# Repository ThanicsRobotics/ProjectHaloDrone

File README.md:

# ProjectHalo
This is the official repository of the Thanics Halo open-source project. This is a project powered by the Raspberry Pi Compute Module 3, both the drone and controller use this module, along with several coprocessors. This project is not complete yet and all documaentation has not been uploaded, but feel free to follow along with our progress or use any of our 3D parts or software, as long as you attribute us.
## Background
### The Drone
The Thanics Halo drone utilizes stereo camera vision and ultrasonic sensors to accomplish spherical obstacle avoidance. The Halo drone is built to be versatile with a variety of cameras of different imaging types. The project focuses primarily on 360 (spherical) imaging and spherical video live streaming.

### The Controller
The controller for the Halo drone is equally as innovative as the drone. This is a hybrid controller, able to be used either with two thumbs (traditional), or wrist-mounted for voice or touchscreen control.

## Files
### Software: 
Drone source code is in this repository, the controller code can be found here: https://github.com/ThanicsRobotics/ProjectHaloController
### For ECAD and MCAD Files:
Go to our other repository here: https://github.com/ThanicsRobotics/ProjectHaloCAD

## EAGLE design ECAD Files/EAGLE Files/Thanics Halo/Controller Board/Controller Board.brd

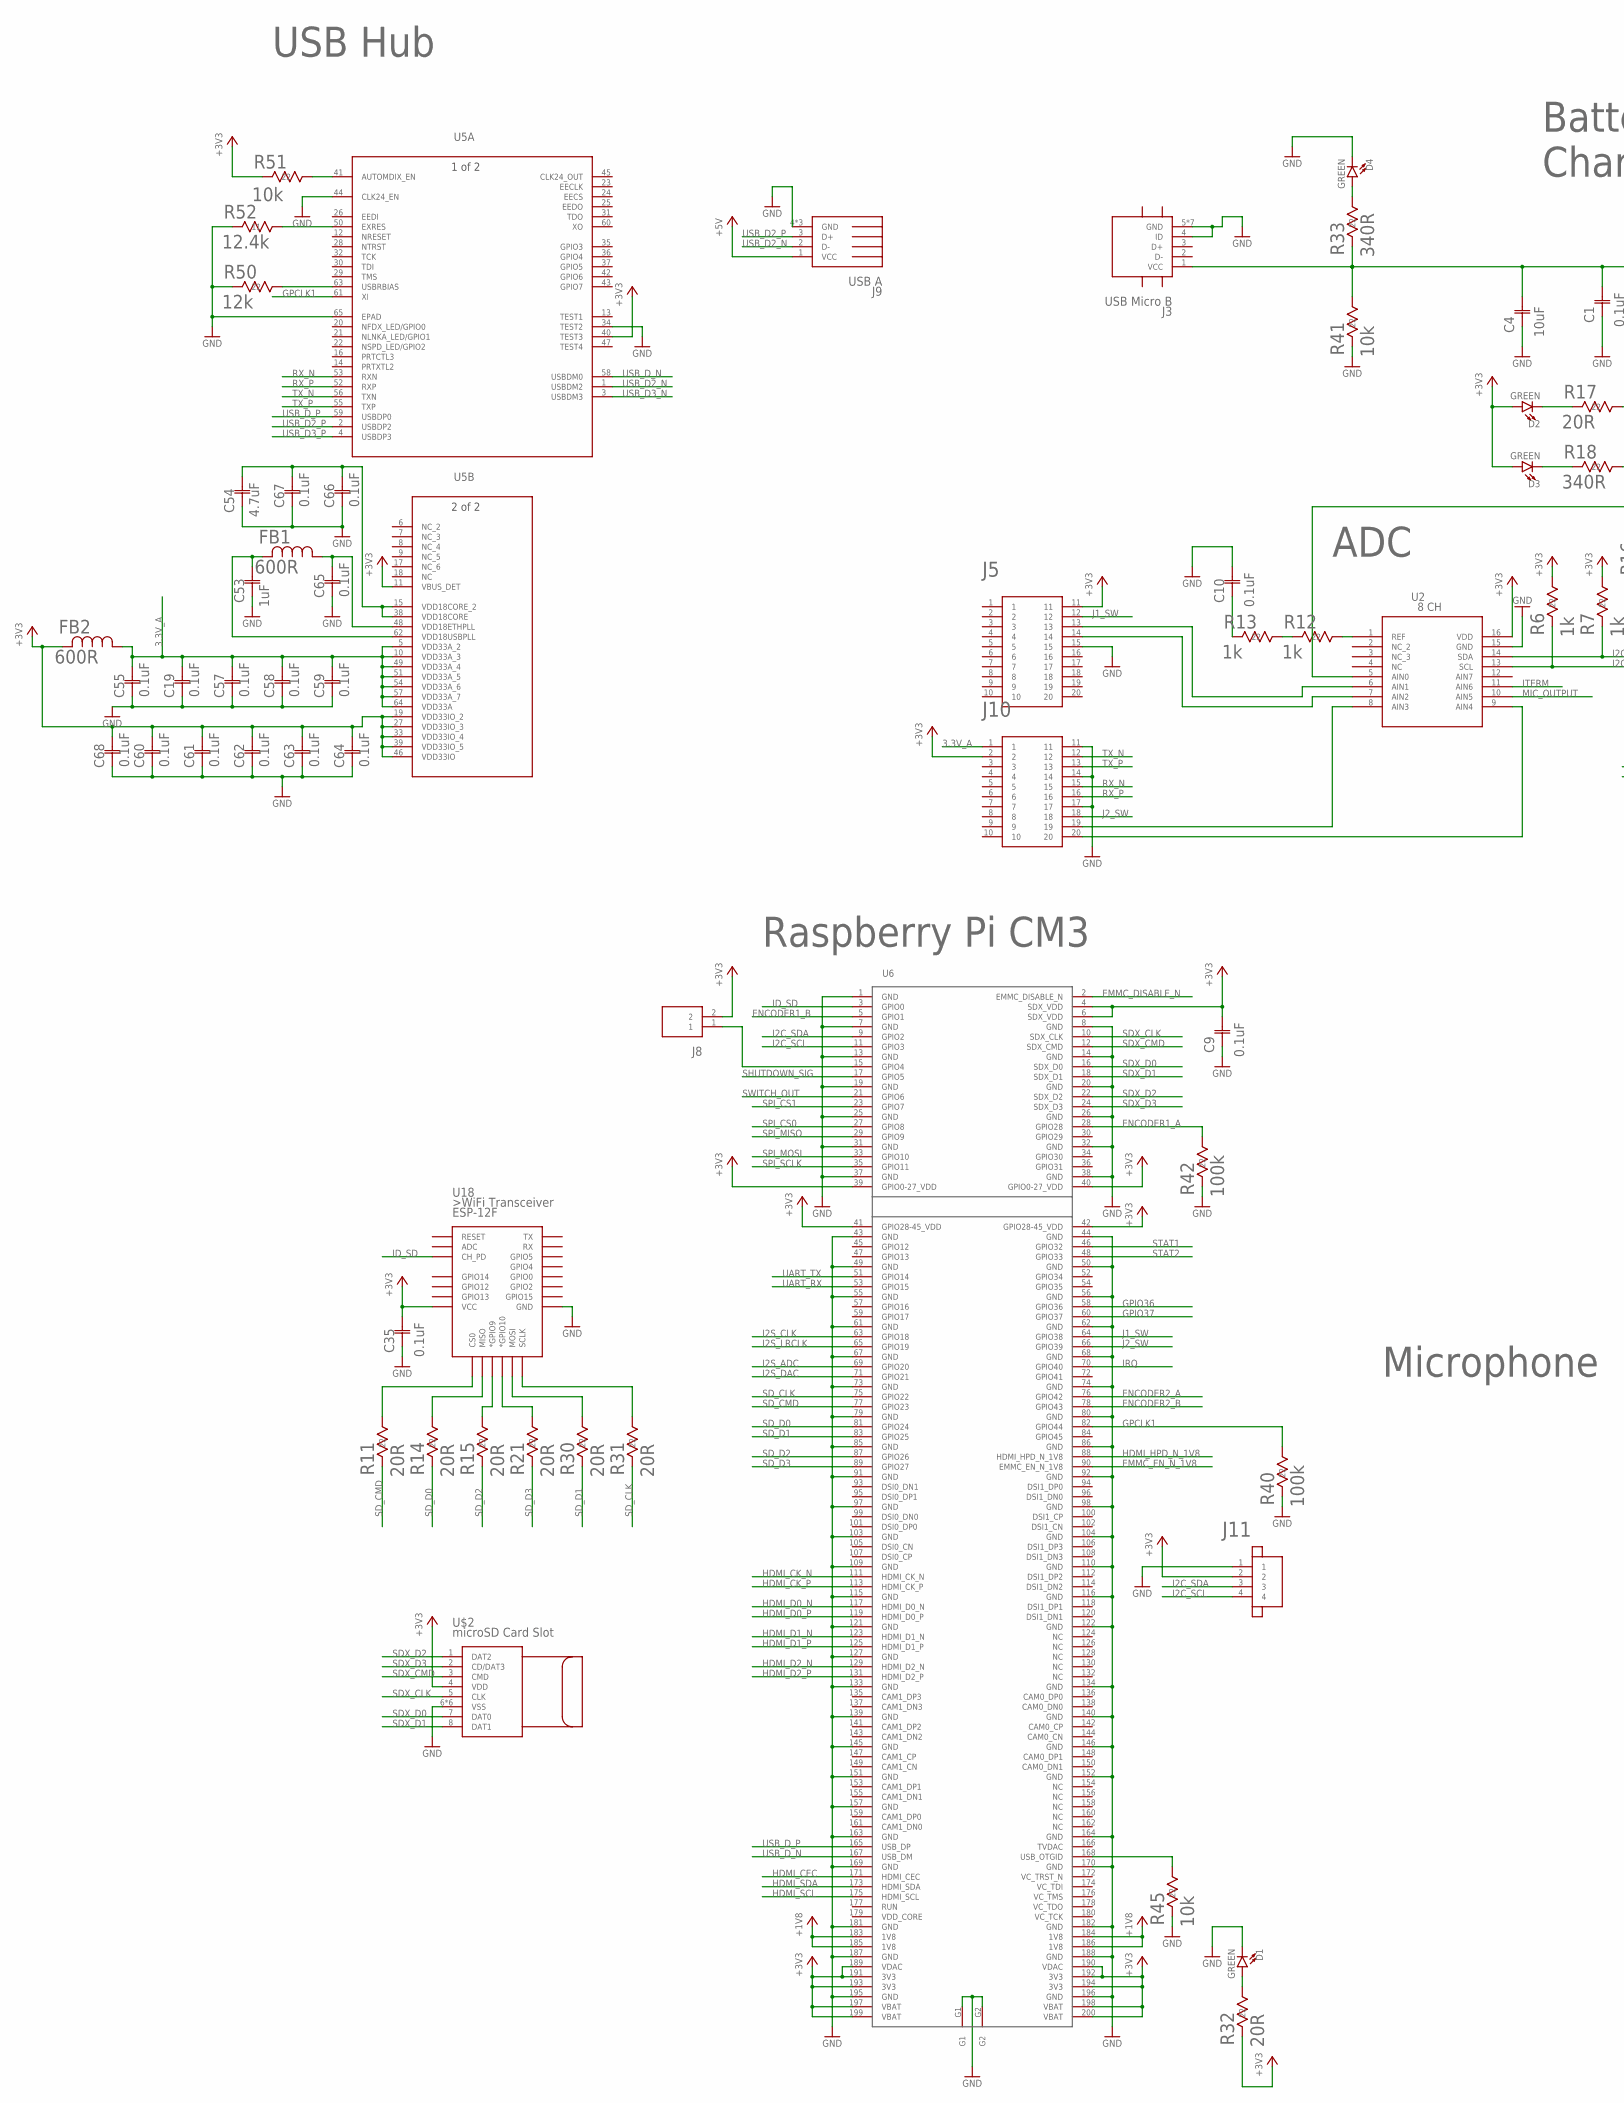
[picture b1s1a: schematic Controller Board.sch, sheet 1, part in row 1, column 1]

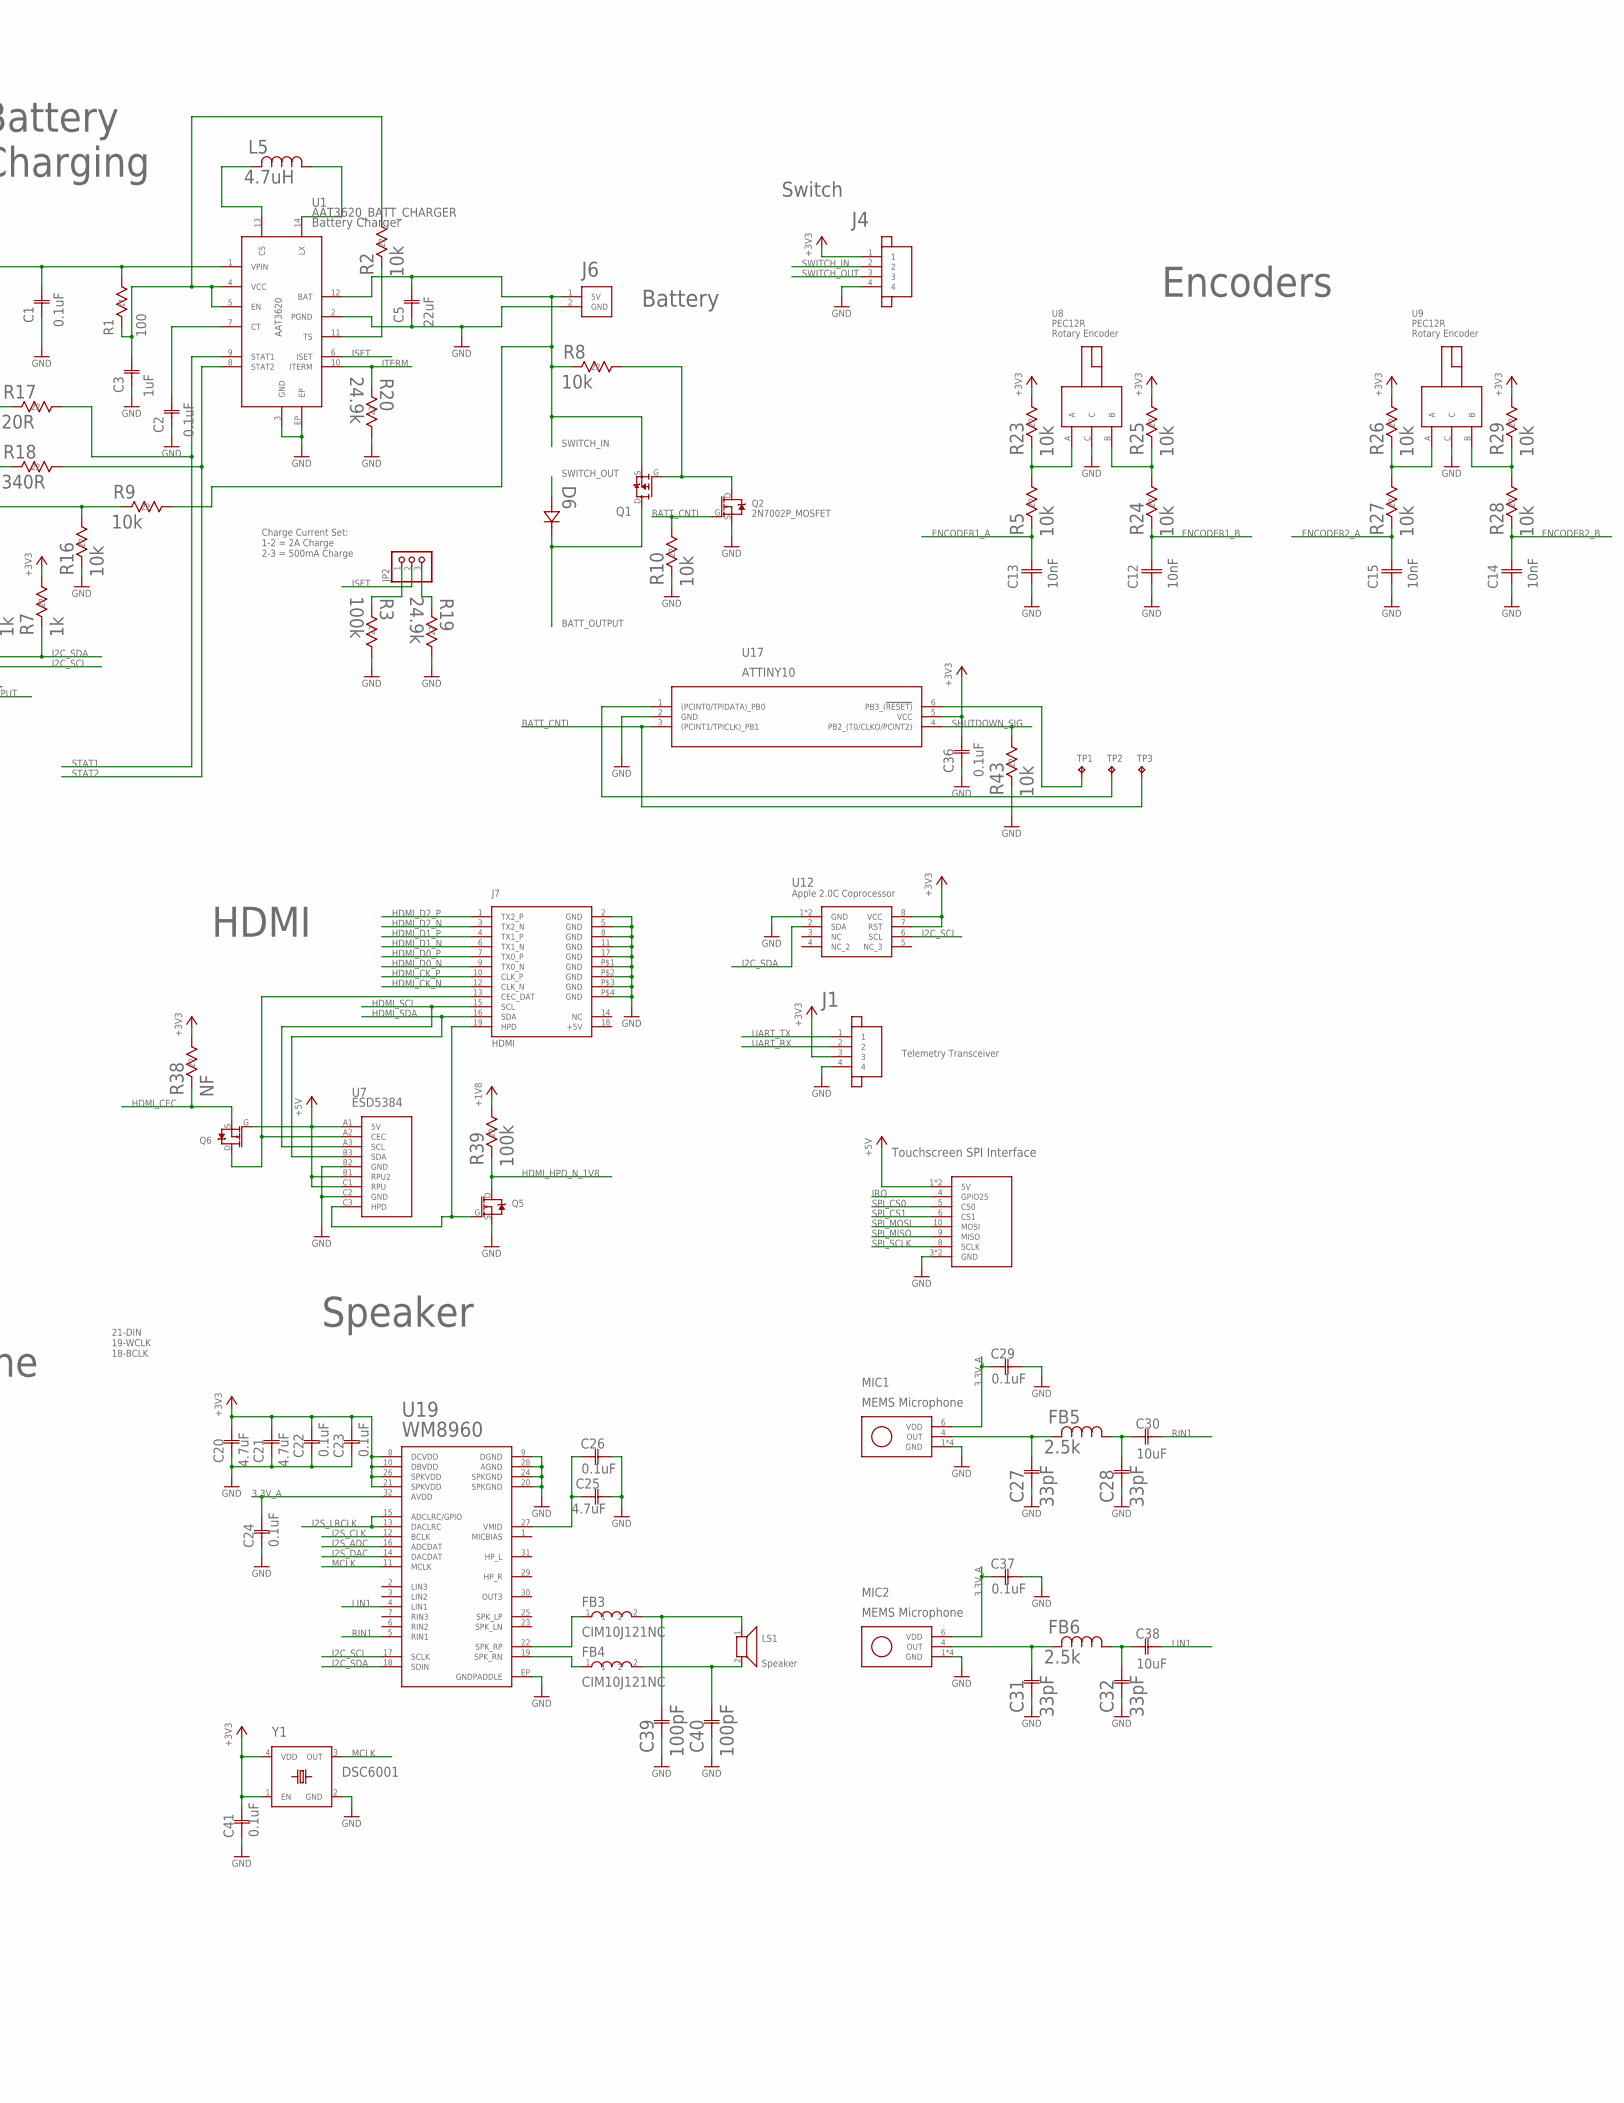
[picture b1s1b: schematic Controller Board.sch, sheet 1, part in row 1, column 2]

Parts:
C1, C2, C9, C10, C35, C36: 0.1uF; 0805
C3, C53: 1uF; YAG_CC0805
C4, C30, C38: 10uF; G-21
C5: 22uF; G-21
C12, C13, C14, C15: 10nF; 0603_CAPACITOR
C19, C22, C23, C24, C26, C29, C37, C41, C55, C57, C58, C59, C60, C61, C62, C63, C64, C65, C66, C67, C68: 0.1uF; 0402-M
C20, C21, C25, C54: 4.7uF; 0603-M
C27, C28, C31, C32: 33pF; G-155-M
C39, C40: 100pF; YAG_CC0402-M
D1, D2, D3, D4: GREEN; LED-0603
D6: 1N4148W-7-FSOD123-M; SOD123-M
FB1, FB2: 600R; IND_BLM18_0603-M
FB3, FB4: CIM10J121NC; 0603_CAPACITOR
FB5, FB6: 2.5k; IND_BLM18_0603-M
J1, J4, J11: JST_SH_4POS
J2: 3.5_TOUCHSCREEN
J3: USB_MICRO_B_SMT
J5, J10: EDGE_CONNECTOR_20POS
J6: POWER_CONNECTOR; XH_CONNECTOR
J7: HDMI
J8: 2_PIN_CONNECTOR; XH_CONNECTOR
J9: USB_A_RECEPT
JP2: PINHD-1X3; 1X03
L5: 4.7uH; 1008
LS1: SP-1510; SPEAKER
MIC1, MIC2: SPH1642HT5H-1; SISONIC_MICROPHONE
Q1: DMP3099L; SOT-23_(TO-236AB)
Q2: 2N7002P_MOSFET; SOT-23_(TO-236AB)
Q5, Q6: DMG1012T; SOT-523
R1: 100; 1206
R2, R5, R8, R9, R10, R16, R23, R24, R25, R26, R27, R28, R29, R41, R43, R45, R51: 10k; RC0805N
R3, R39, R40, R42: 100k; RC0603N-M
R6, R7, R12, R13: 1k; RC0603N-M
R11, R14, R15, R17, R21, R30, R31, R32: 20R; RC0603N-M
R18, R33: 340R; RC0603N
R19, R20: 24.9k; RC0402N-M
R38: NF; RC0805N
R50: 12k; RC0402N-M
R52: 12.4k; YAG_R0402-M
TP1, TP2, TP3: TPB2,54; B2,54
U1: AAT3620_BATT_CHARGER; AAT3620_TDFN
U2: 8 CH; 21-0055H_16-M
U5: LAN9512-JZXQFN64_9X9MC-M; QFN64_9X9MC-M
U6: COMPUTE_MODULE; SO-DIMM
U7: ESD5384; WLCSP9
U8, U9: PEC12R
U12: APPLE_2.0C_COPROCESSOR; PG-USON-8-1
U17: ATTINY10-TSHR6ST1-M; 6ST1-M
U18: ESP12ESMD; ESP12E-SMD
U19: WM8960; 32QFN
U$2: MICROSD
Y1: DSC6001; 4-VFLGA

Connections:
3.3V_A: C19.2, C24.2, C29.1, C37.1, C55.2, C57.2, C58.2, C59.2, FB2.1, J10.1, MIC1.6 (VDD), MIC2.6 (VDD), U5.5 (VDD33A_2), U5.10 (VDD33A_3), U5.49 (VDD33A_4), U5.51 (VDD33A_5), U5.54 (VDD33A_6), U5.57 (VDD33A_7), U5.64 (VDD33A), U19.32 (AVDD)
+1V8: R39.1 (11), U6.183 (1V8), U6.184 (1V8), U6.185 (1V8), U6.186 (1V8); also elsewhere on the board
+3V3: C9.2, C20.2, C21.2, C22.2, C23.2, C35.2, C36.2, C41.2, C60.2, C61.2, C62.2, C63.2, C64.2, C68.2, D2.A, D3.A, FB2.2, J1.3, J4.1, J5.11, J8.2, J10.2, J11.2, R6.1 (11), R7.1 (11), R23.1 (11), R25.1 (11), R26.1 (11), R29.1 (11), R32.2 (22), R38.1 (11), R51.2 (22), U2.16 (VDD), U5.11 (VBUS_DET), U5.19 (VDD33IO_2), U5.27 (VDD33IO_3), U5.33 (VDD33IO_4), U5.39 (VDD33IO_5), U5.40 (TEST3), U5.46 (VDD33IO), U6.4 (SDX_VDD), U6.6 (SDX_VDD), U6.39 (GPIO0-27_VDD), U6.40 (GPIO0-27_VDD), U6.41 (GPIO28-45_VDD), U6.42 (GPIO28-45_VDD), U6.189 (VDAC), U6.190 (VDAC), U6.191 (3V3), U6.192 (3V3), U6.193 (3V3), U6.194 (3V3), U6.197 (VBAT), U6.198 (VBAT), U6.199 (VBAT), U6.200 (VBAT), U12.7 (RST), U12.8 (VCC), U17.5 (VCC), U18.VCC, U19.8 (DCVDD), U19.10 (DBVDD), U19.21 (SPKVDD), U19.26 (SPKVDD), U$2.4 (VDD), Y1.1 (EN), Y1.4 (VDD); also elsewhere on the board
+5V: J2.1 (5V), J2.2 (5V), J9.1 (VCC), Q6.G, U7.A1 (5V), U7.B1 (RPU2), U7.C1 (RPU); also elsewhere on the board
BATT_CNTL: Q2.G, R10.1 (11), TP3.TP, U17.3 ((PCINT1/TPICLK)_PB1)
BATT_OUTPUT: D6.C (12), Q1.D; also elsewhere on the board
EMMC_DISABLE_N: U6.2 (EMMC_DISABLE_N)
EMMC_EN_N_1V8: U6.90 (EMMC_EN_N_1V8)
ENCODER1_A: C13.2, R5.2 (22), R42.1 (11), U6.28 (GPIO28)
ENCODER1_B: C12.2, R24.2 (22), U6.5 (GPIO1)
ENCODER2_A: C15.2, R27.2 (22), U6.76 (GPIO42)
ENCODER2_B: C14.2, R28.2 (22), U6.78 (GPIO43)
GND: C1.1, C2.1, C3.1, C4.1, C5.1, C9.1, C10.2, C12.1, C13.1, C14.1, C15.1, C19.1, C20.1, C21.1, C22.1, C23.1, C24.1, C25.2, C26.2, C27.1 (11), C28.1 (11), C29.2, C31.1 (11), C32.1 (11), C35.1, C36.1, C37.2, C39.1 (11), C40.1 (11), C41.1, C53.1 (11), C54.1, C55.1, C57.1, C58.1, C59.1, C60.1, C61.1, C62.1, C63.1, C64.1, C65.1, C66.1, C67.1, C68.1, D1.C, D4.C, J1.4, J2.3 (GND), J2.7 (GND), J3.4 (ID), J3.5 (GND), J3.6 (GND), J3.7 (GND), J3.P$1 (GND), J3.P$2 (GND), J3.P$3 (GND), J3.P$4 (GND), J4.4, J5.15, J6.2 (GND), J7.2 (GND), J7.5 (GND), J7.8 (GND), J7.11 (GND), J7.17 (GND), J7.P$1 (GND), J7.P$2 (GND), J7.P$3 (GND), J7.P$4 (GND), J9.4 (GND), J9.5 (GND), J9.6 (GND), J10.11, J10.14, J10.17, J11.1, MIC1.1 (GND), MIC1.2 (GND), MIC1.3 (GND), MIC1.5 (GND), MIC2.1 (GND), MIC2.2 (GND), MIC2.3 (GND), MIC2.5 (GND), Q2.S, Q5.S, R3.1 (11), R10.2 (22), R16.2 (22), R19.1 (11), R20.1 (11), R40.2 (22), R41.2 (22), R42.2 (22), R43.2 (22), R45.2 (22), R50.2 (22), R52.1 (11), U1.2 (PGND), U1.3 (GND), U1.EP, U2.15 (GND), U5.34 (TEST2), U5.44 (CLK24_EN), U5.65 (EPAD), U6.1 (GND), U6.7 (GND), U6.8 (GND), U6.13 (GND), U6.14 (GND), U6.19 (GND), U6.20 (GND), U6.25 (GND), U6.26 (GND), U6.31 (GND), U6.32 (GND), U6.37 (GND), U6.38 (GND), U6.43 (GND), U6.44 (GND), U6.49 (GND), U6.50 (GND), U6.55 (GND), U6.56 (GND), U6.61 (GND), U6.62 (GND), U6.67 (GND), U6.68 (GND), U6.73 (GND), U6.74 (GND), U6.79 (GND), U6.80 (GND), U6.85 (GND), U6.86 (GND), U6.91 (GND), U6.92 (GND), U6.97 (GND), U6.98 (GND), U6.103 (GND), U6.104 (GND), U6.109 (GND), U6.110 (GND), U6.115 (GND), U6.116 (GND), U6.121 (GND), U6.122 (GND), U6.127 (GND), U6.133 (GND), U6.134 (GND), U6.139 (GND), U6.140 (GND), U6.145 (GND), U6.146 (GND), U6.151 (GND), U6.152 (GND), U6.157 (GND), U6.163 (GND), U6.164 (GND), U6.169 (GND), U6.170 (GND), U6.181 (GND), U6.182 (GND), U6.187 (GND), U6.188 (GND), U6.195 (GND), U6.196 (GND), U6.G1, U6.G2, U7.B2 (GND), U7.C2 (GND), U8.C, U9.C, U12.1 (GND), U12.9 (GND), U17.2 (GND), U18.GND, U19.9 (DGND), U19.20 (SPKGND), U19.24 (SPKGND), U19.28 (AGND), U19.EP (GNDPADDLE), U$2.6 (VSS), U$2.9 (VSS), U$2.10 (VSS), U$2.11 (VSS), U$2.12 (VSS), U$2.13 (VSS), Y1.2 (GND); also elsewhere on the board
GPCLK1: R40.1 (11), U5.61 (XI), U6.82 (GPIO44)
GPIO36: U6.58 (GPIO36)
GPIO37: U6.60 (GPIO37)
HDMI_CEC: Q6.S, R38.2 (22), U6.171 (HDMI_CEC)
HDMI_CK_N: J7.12 (CLK_N), U6.111 (HDMI_CK_N)
HDMI_CK_P: J7.10 (CLK_P), U6.113 (HDMI_CK_P)
HDMI_D0_N: J7.9 (TX0_N), U6.117 (HDMI_D0_N)
HDMI_D0_P: J7.7 (TX0_P), U6.119 (HDMI_D0_P)
HDMI_D1_N: J7.6 (TX1_N), U6.123 (HDMI_D1_N)
HDMI_D1_P: J7.4 (TX1_P), U6.125 (HDMI_D1_P)
HDMI_D2_N: J7.3 (TX2_N), U6.129 (HDMI_D2_N)
HDMI_D2_P: J7.1 (TX2_P), U6.131 (HDMI_D2_P)
HDMI_HPD_N_1V8: Q5.D, R39.2 (22), U6.88 (HDMI_HPD_N_1V8)
HDMI_SCL: J7.15 (SCL), U6.175 (HDMI_SCL), U7.A3 (SCL)
HDMI_SDA: J7.16 (SDA), U6.173 (HDMI_SDA), U7.B3 (SDA)
I2C_SCL: J11.4, R6.2 (22), U2.13 (SCL), U6.11 (GPIO3), U12.6 (SCL), U19.17 (SCLK)
I2C_SDA: J11.3, R7.2 (22), U2.14 (SDA), U6.9 (GPIO2), U12.2 (SDA), U19.18 (SDIN)
I2S_ADC: U6.69 (GPIO20), U19.16 (ADCDAT)
I2S_CLK: U6.63 (GPIO18), U19.12 (BCLK)
I2S_DAC: U6.71 (GPIO21), U19.14 (DACDAT)
I2S_LRCLK: U6.65 (GPIO19), U19.13 (DACLRC), U19.15 (ADCLRC/GPIO)
ID_SD: U6.3 (GPIO0), U18.CH_PD
IRQ: J2.4 (GPIO25), U6.70 (GPIO40)
ISET: JP2.2, U1.6 (ISET)
ITERM: R20.2 (22), U1.10 (ITERM), U2.11 (AIN6)
J1_SW: J5.12, U6.64 (GPIO38)
J2_SW: J10.18, U6.66 (GPIO39)
LIN1: C38.2 (22), U19.4 (LIN1)
MCLK: U19.11 (MCLK), Y1.3 (OUT)
MIC_OUTPUT: U2.10 (AIN5)
unnamed: TP1.TP, U17.6 (PB3_(!RESET))
unnamed: C2.2, U1.7 (CT)
unnamed: R14.1 (11), U18.MISO
unnamed: L5.P$2 (2), U1.13 (CS)
unnamed: L5.P$1 (1), U1.14 (LX)
unnamed: C3.2, R1.1 (11), R2.1 (11), U1.4 (VCC), U1.5 (EN)
unnamed: R11.1 (11), U18.CS0
unnamed: D4.A, R33.1 (11)
unnamed: D1.A, R32.1 (11)
unnamed: R2.2 (22), U1.11 (TS)
unnamed: C25.1, C26.1, U19.27 (VMID)
unnamed: D2.C, R17.2 (22)
unnamed: R12.1 (11), U2.1 (REF)
unnamed: J5.13, U2.6 (AIN1)
unnamed: J5.14, U2.7 (AIN2)
unnamed: J10.19, U2.8 (AIN3)
unnamed: J10.20, U2.9 (AIN4)
unnamed: C27.2 (22), FB5.2, MIC1.4 (OUT)
unnamed: D3.C, R18.2 (22)
unnamed: R12.2 (22), R13.1 (11)
unnamed: R15.1 (11), U18.GPIO9 (*GPIO9)
unnamed: R21.1 (11), U18.GPIO10 (*GPIO10)
unnamed: R30.1 (11), U18.MOSI
unnamed: C10.1, R13.2 (22)
unnamed: R5.1 (11), R23.2 (22), U8.A
unnamed: C28.2 (22), C30.1 (11), FB5.1
unnamed: R24.1 (11), R25.2 (22), U8.B
unnamed: C31.2 (22), FB6.2, MIC2.4 (OUT)
unnamed: C32.2 (22), C38.1 (11), FB6.1
unnamed: R26.2 (22), R27.1 (11), U9.A
unnamed: R28.1 (11), R29.2 (22), U9.B
unnamed: R9.2 (22), R16.1 (11), U2.5 (AIN0)
unnamed: JP2.1, R3.2 (22)
unnamed: FB4.1, U19.19 (SPK_RN)
unnamed: JP2.3, R19.2 (22)
unnamed: FB3.1, U19.22 (SPK_RP)
unnamed: C39.2 (22), FB3.2, LS1.1
unnamed: C40.2 (22), FB4.2, LS1.2
unnamed: R31.1 (11), U18.SCLK
unnamed: J7.13 (CEC_DAT), Q6.D, U7.A2 (CEC)
unnamed: J7.19 (HPD), Q5.G, U7.C3 (HPD)
unnamed: R45.1 (11), U6.168 (USB_OTGID)
unnamed: J8.1, U6.15 (GPIO4)
unnamed: R51.1 (11), U5.41 (AUTOMDIX_EN)
unnamed: R50.1 (11), U5.63 (USBRBIAS)
unnamed: Q1.G, Q2.D, R8.1 (11)
unnamed: C65.2, FB1.1, U5.48 (VDD18ETHPLL)
unnamed: C53.2 (22), FB1.2, U5.62 (VDD18USBPLL)
unnamed: R52.2 (22), U5.50 (EXRES)
unnamed: C54.2, C66.2, C67.2, U5.15 (VDD18CORE_2), U5.38 (VDD18CORE)
PB0: TP2.TP, U17.1 ((PCINT0/TPIDATA)_PB0)
RIN1: C30.2 (22), U19.5 (RIN1)
RX_N: J10.15, U5.53 (RXN)
RX_P: J10.16, U5.52 (RXP)
SDX_CLK: U6.10 (SDX_CLK), U$2.5 (CLK)
SDX_CMD: U6.12 (SDX_CMD), U$2.3 (CMD)
SDX_D0: U6.16 (SDX_D0), U$2.7 (DAT0)
SDX_D1: U6.18 (SDX_D1), U$2.8 (DAT1)
SDX_D2: U6.22 (SDX_D2), U$2.1 (DAT2)
SDX_D3: U6.24 (SDX_D3), U$2.2 (CD/DAT3)
SD_CLK: R31.2 (22), U6.75 (GPIO22)
SD_CMD: R11.2 (22), U6.77 (GPIO23)
SD_D0: R14.2 (22), U6.81 (GPIO24)
SD_D1: R30.2 (22), U6.83 (GPIO25)
SD_D2: R15.2 (22), U6.87 (GPIO26)
SD_D3: R21.2 (22), U6.89 (GPIO27)
SHUTDOWN_SIG: R43.1 (11), U6.17 (GPIO5), U17.4 (PB2_(T0/CLKO/PCINT2))
SPI_CS0: J2.5 (CS0), U6.27 (GPIO8)
SPI_CS1: J2.6 (CS1), U6.23 (GPIO7)
SPI_MISO: J2.9 (MISO), U6.29 (GPIO9)
SPI_MOSI: J2.10 (MOSI), U6.33 (GPIO10)
SPI_SCLK: J2.8 (SCLK), U6.35 (GPIO11)
STAT1: R17.1 (11), U1.9 (STAT1), U6.46 (GPIO32)
STAT2: R18.1 (11), U1.8 (STAT2), U6.48 (GPIO33)
SWITCH_IN: C5.2, J4.2, J6.1 (5V), Q1.S, R8.2 (22), R9.1 (11), U1.12 (BAT)
SWITCH_OUT: D6.A (21), J4.3, U6.21 (GPIO6)
TX_N: J10.12, U5.56 (TXN)
TX_P: J10.13, U5.55 (TXP)
UART_RX: J1.2, U6.53 (GPIO15)
UART_TX: J1.1, U6.51 (GPIO14)
USB_5V: C1.2, C4.2, J3.1 (VCC), R1.2 (22), R33.2 (22), R41.1 (11), U1.1 (VPIN)
USB_D2_N: J9.2 (D-), U5.1 (USBDM2)
USB_D2_P: J9.3 (D+), U5.2 (USBDP2)
USB_D3_N: U5.3 (USBDM3)
USB_D3_P: U5.4 (USBDP3)
USB_D_N: U5.58 (USBDM0), U6.167 (USB_DM)
USB_D_P: U5.59 (USBDP0), U6.165 (USB_DP)

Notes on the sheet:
Battery
Switch
Telemetry Transceiver
Charge Current Set: 1-2 = 2A Charge 2-3 = 500mA Charge
HDMI
Battery Charging
USB Hub
Encoders
Microphone
Speaker
ADC
Raspberry Pi CM3
21-DIN 19-WCLK 18-BCLK

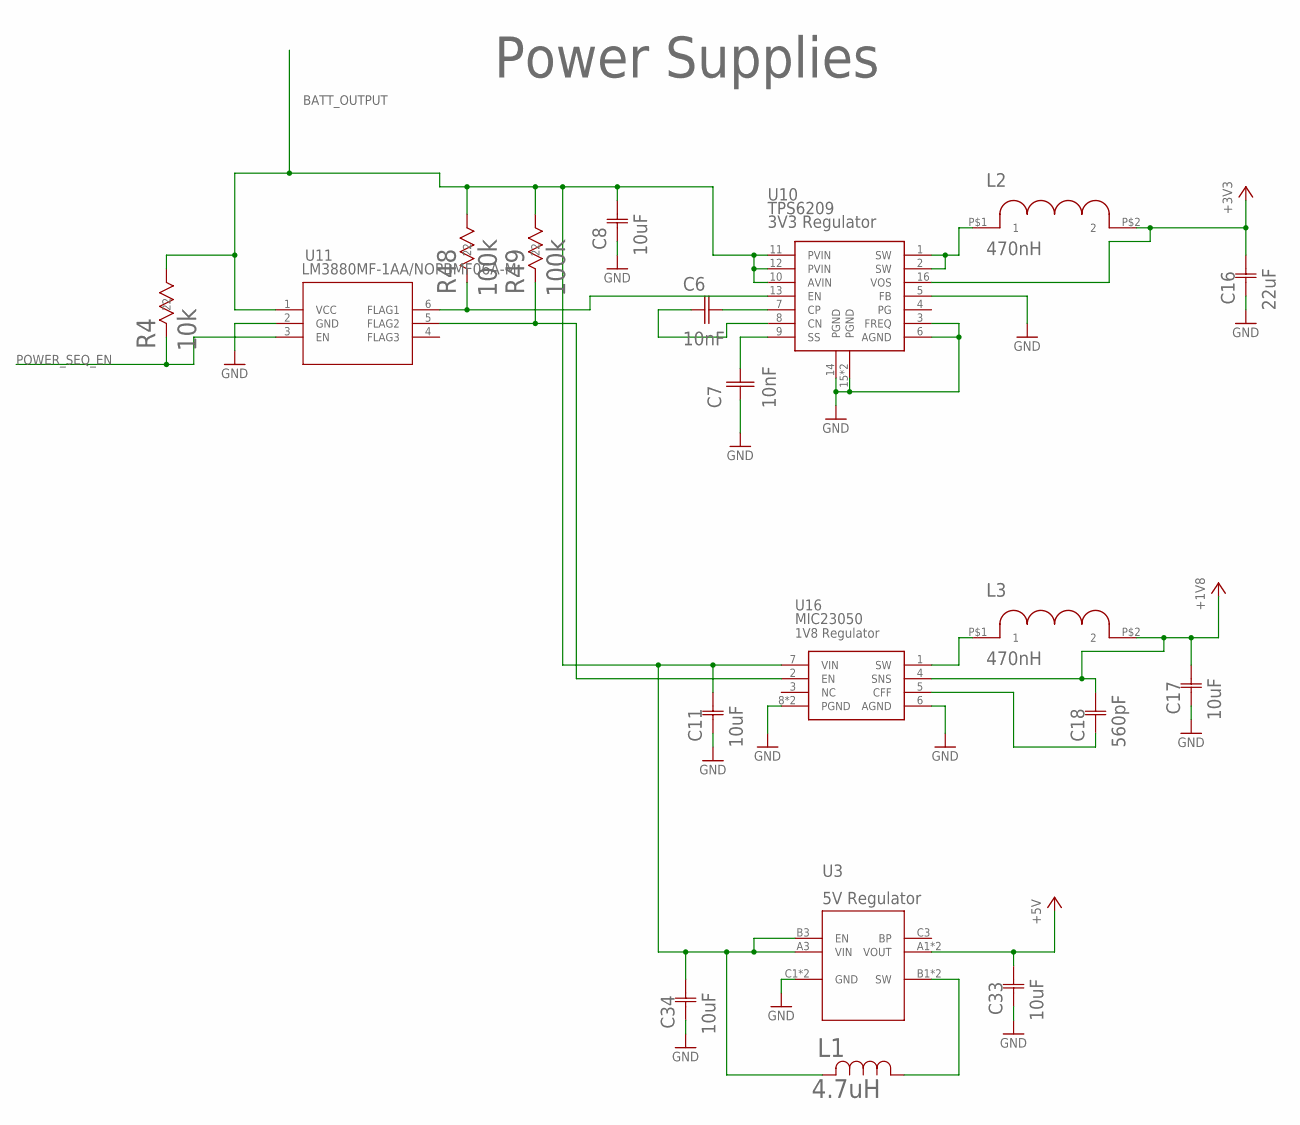
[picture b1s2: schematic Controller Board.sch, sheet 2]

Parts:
C6, C7: 10nF; 0603_CAPACITOR
C8, C11, C17, C33, C34: 10uF; G-21
C16: 22uF; G-21
C18: 560pF; CC0402N-M
L1: 4.7uH; 1008
L2, L3: 470nH; 470NH_INDUCTOR
R4: 10k; RC0805N
R48, R49: 100k; RC0603N-M
U3: TPS61256YFFR; YFF9
U10: TPS6209; VQFN16
U11: LM3880MF-1AA/NOPBMF06A-M; MF06A-M
U16: MIC23050; MLF(ML)_8PIN

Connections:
+1V8: C17.2, C18.2, L3.P$2 (2), U16.4 (SNS); also elsewhere on the board
+3V3: C16.2, L2.P$2 (2), U10.16 (VOS); also elsewhere on the board
+5V: C33.2, U3.A1 (VOUT), U3.A2 (VOUT); also elsewhere on the board
BATT_OUTPUT: C8.2, C11.2, C34.2, L1.P$2 (2), R4.1 (11), R48.1 (11), R49.1 (11), U3.A3 (VIN), U3.B3 (EN), U10.10 (AVIN), U10.11 (PVIN), U10.12 (PVIN), U11.1 (VCC), U16.7 (VIN); also elsewhere on the board
GND: C7.1, C8.1, C11.1, C16.1, C17.1, C33.1, C34.1, U3.C1 (GND), U3.C2 (GND), U10.3 (FREQ), U10.5 (FB), U10.6 (AGND), U10.14 (PGND), U10.15 (PGND), U10.17 (PGND), U11.2 (GND), U16.6 (AGND), U16.8 (PGND), U16.EP (PGND); also elsewhere on the board
unnamed: R48.2 (22), U10.13 (EN), U11.6 (FLAG1)
unnamed: R49.2 (22), U11.5 (FLAG2), U16.2 (EN)
unnamed: C6.2, U10.7 (CP)
unnamed: C6.1, U10.8 (CN)
unnamed: C7.2, U10.9 (SS)
unnamed: L2.P$1 (1), U10.1 (SW), U10.2 (SW)
unnamed: L3.P$1 (1), U16.1 (SW)
unnamed: C18.1, U16.5 (CFF)
unnamed: L1.P$1 (1), U3.B1 (SW), U3.B2 (SW)
POWER_SEQ_EN: R4.2 (22), U11.3 (EN)

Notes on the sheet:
Power Supplies

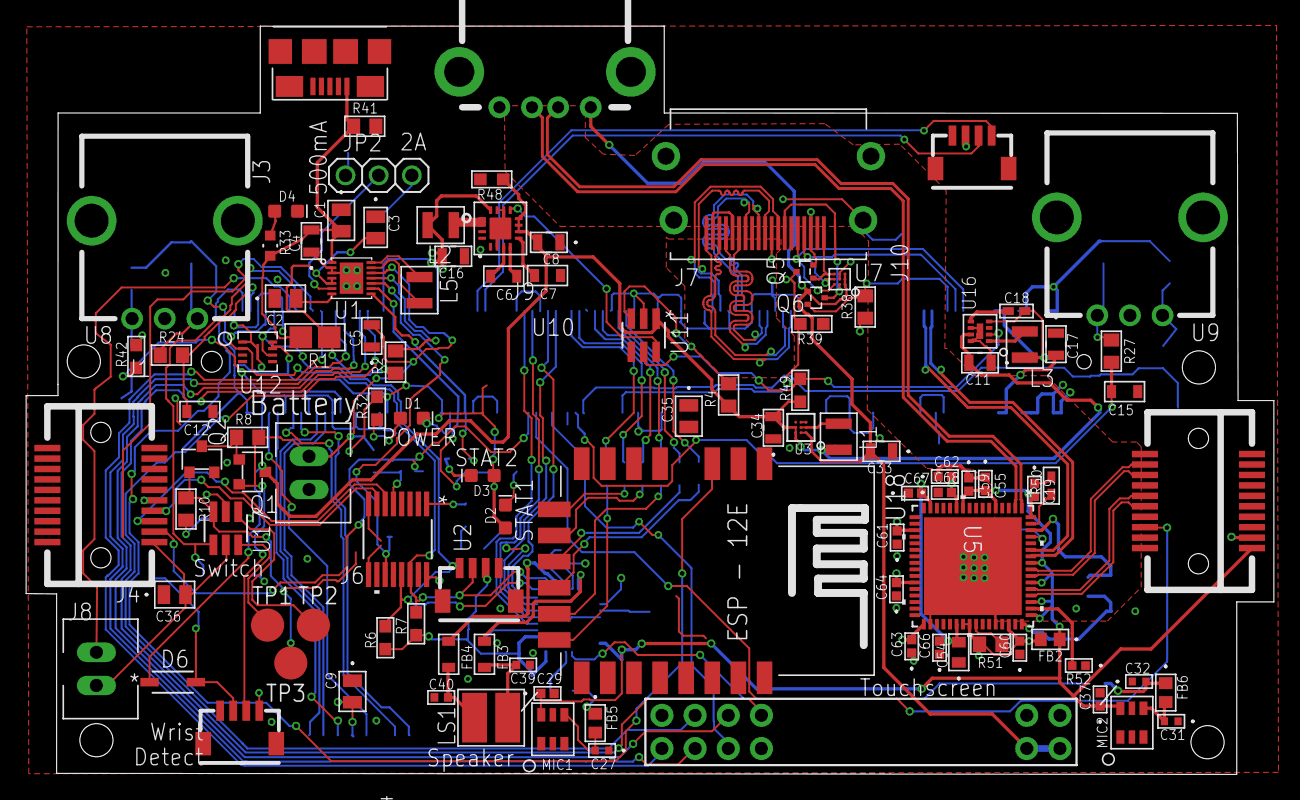
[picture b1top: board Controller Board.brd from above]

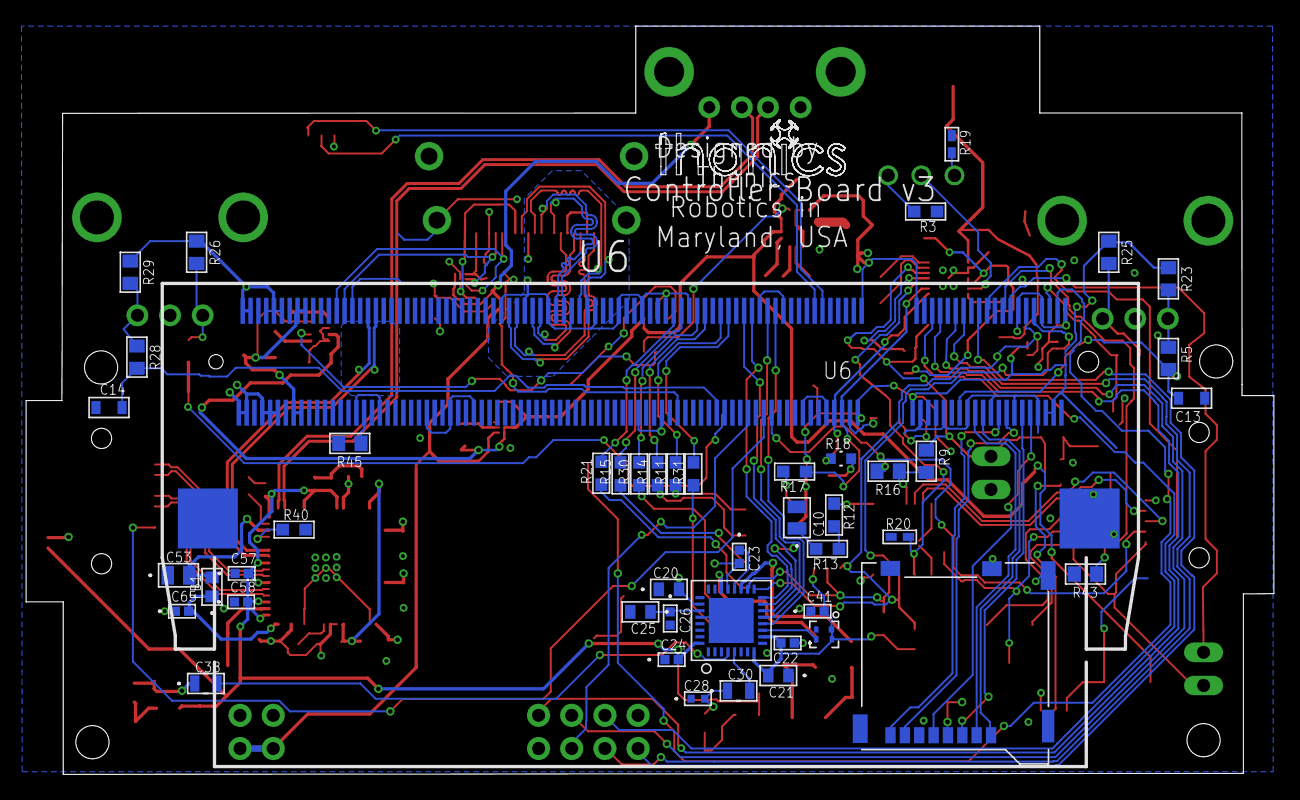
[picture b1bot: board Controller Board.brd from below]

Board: 4 copper layers, 95.6 x 57.3 mm, 154 parts (47 on the bottom side), 133 nets.

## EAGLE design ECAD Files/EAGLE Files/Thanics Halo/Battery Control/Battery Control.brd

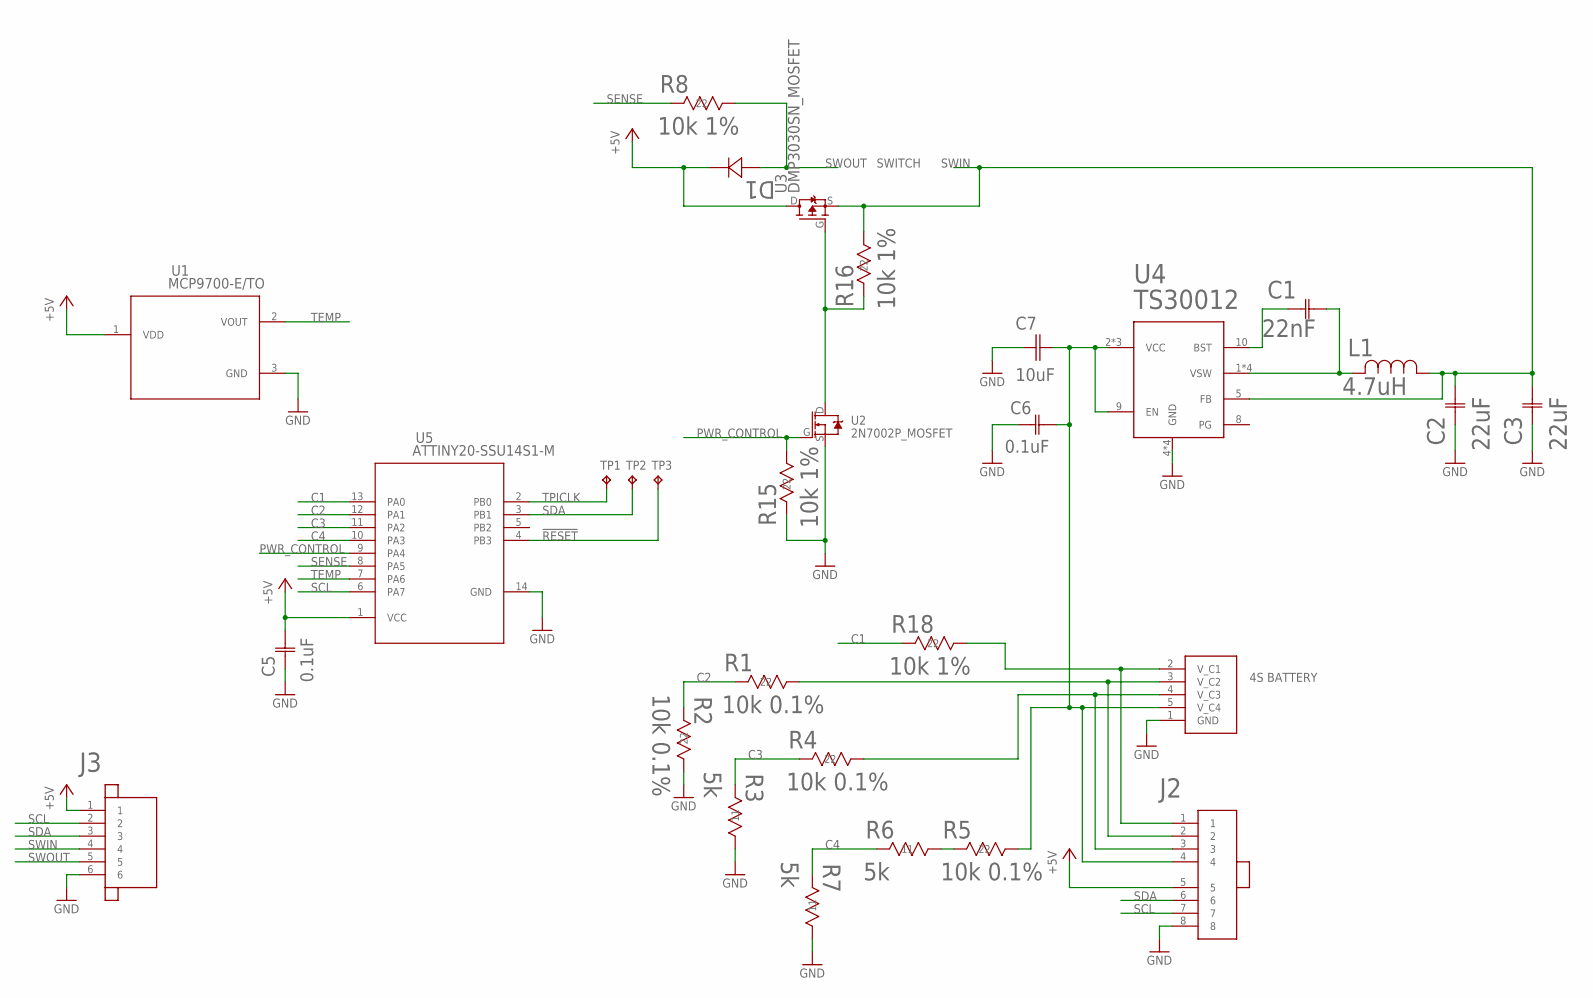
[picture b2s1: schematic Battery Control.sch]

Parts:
C1: 22nF; G-155-M
C2, C3: 22uF; G-21
C5, C6: 0.1uF; 0805
C7: 10uF; 1206_MLCC
D1: 1N4148W-7-FSOD123-M; SOD123-M
J1: JST-XH_5POS
J2: SPRING_BTB_8POS_FEMALE
J3: JST_SH_6POS_SIDE
L1: 4.7uH; 1008
R1, R2, R4, R5: 10k 0.1%; RC0805N
R3, R6, R7: 5k; 0402
R8, R15, R16, R18: 10k 1%; RC0805N
TP1, TP2, TP3: TPB2,54; B2,54
U1: MCP9700-E/TO; TO-92_MC
U2: 2N7002P_MOSFET; SOT-23_(TO-236AB)
U3: DMP3030SN_MOSFET; SC59_MOSFET
U4: TS30012; 16-VQFN
U5: ATTINY20-SSU14S1-M; 14S1-M

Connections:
!RESET: TP3.TP, U5.4 (PB3)
+5V: C5.2, D1.C (12), J2.5, J3.1, U1.1 (VDD), U3.D, U5.1 (VCC)
C1: R18.2 (22), U5.13 (PA0)
C2: R1.2 (22), R2.2 (22), U5.12 (PA1)
C3: R3.1 (11), R4.2 (22), U5.11 (PA2)
C4: R6.1 (11), R7.1 (11), U5.10 (PA3)
GND: C2.1 (11), C3.1 (11), C5.1, C6.1, C7.P$1 (1), J1.1 (GND), J2.8, J3.6, R2.1 (11), R3.2 (22), R7.2 (22), R15.2 (22), U1.3 (GND), U2.S, U4.4 (GND), U4.14 (GND), U4.15 (GND), U4.17 (GND), U5.14 (GND)
unnamed: R16.2 (22), U2.D, U3.G
unnamed: C1.1 (11), U4.10 (BST)
unnamed: C1.2 (22), L1.P$2 (2), U4.1 (VSW), U4.12 (VSW), U4.13 (VSW), U4.16 (VSW)
unnamed: J1.2 (V_C1), J2.1, R18.1 (11)
unnamed: J1.3 (V_C2), J2.2, R1.1 (11)
unnamed: J1.4 (V_C3), J2.3, R4.1 (11)
unnamed: R5.2 (22), R6.2 (22)
unnamed: C6.2, C7.P$2 (2), J1.5 (V_C4), J2.4, R5.1 (11), U4.2 (VCC), U4.3 (VCC), U4.9 (EN), U4.11 (VCC)
PWR_CONTROL: R15.1 (11), U2.G, U5.9 (PA4)
SCL: J2.7, J3.2, U5.6 (PA7)
SDA: J2.6, J3.3, TP2.TP, U5.3 (PB1)
SENSE: R8.2 (22), U5.8 (PA5)
SWIN: C2.2 (22), C3.2 (22), J3.4, L1.P$1 (1), R16.1 (11), U3.S, U4.5 (FB)
SWOUT: D1.A (21), J3.5, R8.1 (11)
TEMP: U1.2 (VOUT), U5.7 (PA6)
TPICLK: TP1.TP, U5.2 (PB0)

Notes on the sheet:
SWITCH

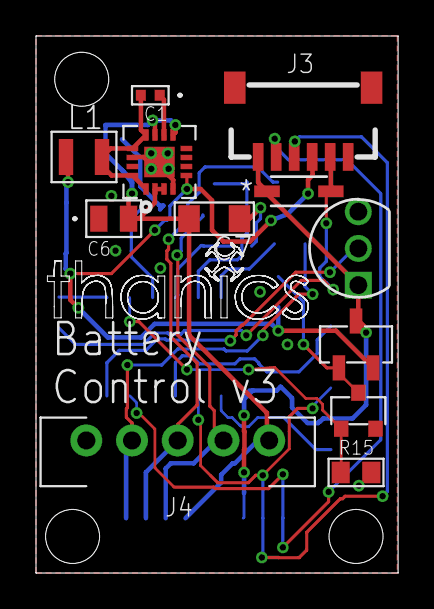
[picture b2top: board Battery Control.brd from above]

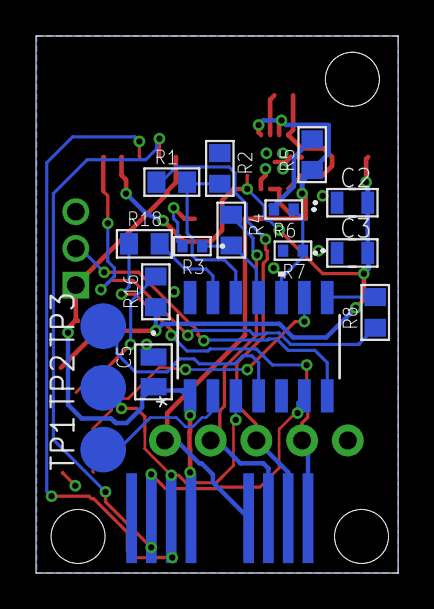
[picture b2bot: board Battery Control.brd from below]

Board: 2 copper layers, 20.1 x 29.8 mm, 30 parts (18 on the bottom side), 23 nets.

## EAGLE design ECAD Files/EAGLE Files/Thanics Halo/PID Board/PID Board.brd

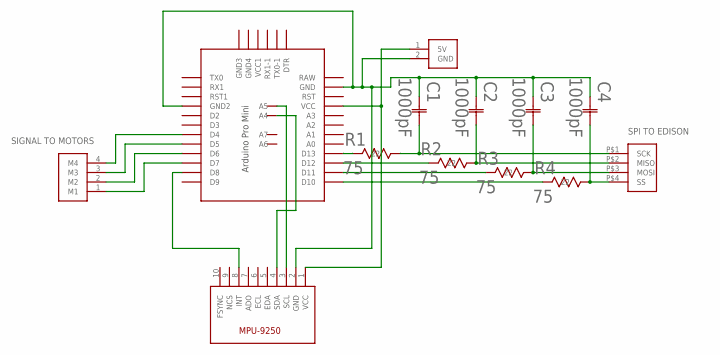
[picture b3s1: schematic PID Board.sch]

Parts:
C1, C2, C3, C4: 1000pF; G-155-M
J1: POWER_CONNECTOR; XH_CONNECTOR
J2: SPI_CONNECTOR; JST-XH_4POS
J3: 4_PIN_CONNECTOR
R1, R2, R3, R4: 75; RC0402N-M
U1: PRO-MINI-2
U2: MPU-9250

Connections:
GND: C1.1 (11), C2.1 (11), C3.1 (11), C4.1 (11), J1.2 (GND), U1.GND, U1.GND1 (GND2), U2.2 (GND)
unnamed: J1.1 (5V), U1.VCC, U2.1 (VCC)
unnamed: R1.2 (22), U1.D13
unnamed: U1.D8, U2.8 (INT)
unnamed: U1.A4, U2.4 (SDA)
unnamed: U1.A5, U2.3 (SCL)
unnamed: R2.2 (22), U1.D12
unnamed: R3.2 (22), U1.D11
unnamed: R4.2 (22), U1.D10
unnamed: C4.2 (22), J2.P$4 (SS), R4.1 (11)
unnamed: J3.1 (M1), U1.D7
unnamed: J3.2 (M2), U1.D6
unnamed: J3.3 (M3), U1.D5
unnamed: J3.4 (M4), U1.D4
unnamed: C3.2 (22), J2.P$3 (MOSI), R3.1 (11)
unnamed: C2.2 (22), J2.P$2 (MISO), R2.1 (11)
unnamed: C1.2 (22), J2.P$1 (SCK), R1.1 (11)

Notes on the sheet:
SIGNAL TO MOTORS
SPI TO EDISON

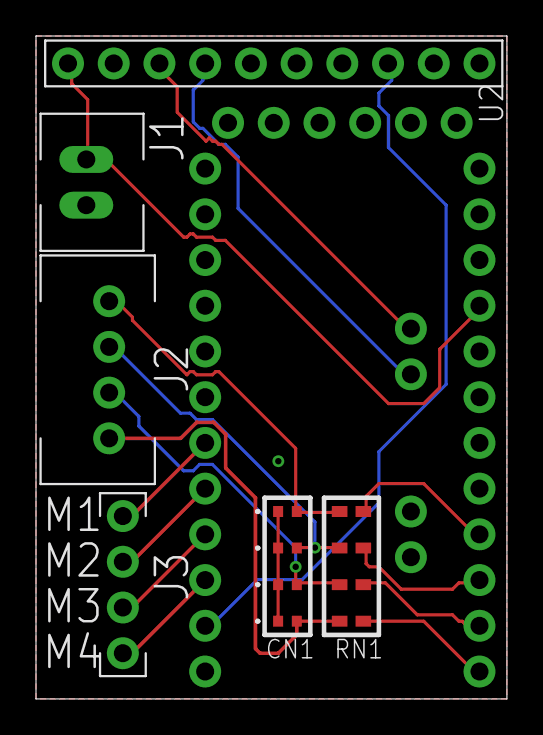
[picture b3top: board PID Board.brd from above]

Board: 2 copper layers, 26.2 x 36.8 mm, 13 parts (0 on the bottom side), 17 nets.

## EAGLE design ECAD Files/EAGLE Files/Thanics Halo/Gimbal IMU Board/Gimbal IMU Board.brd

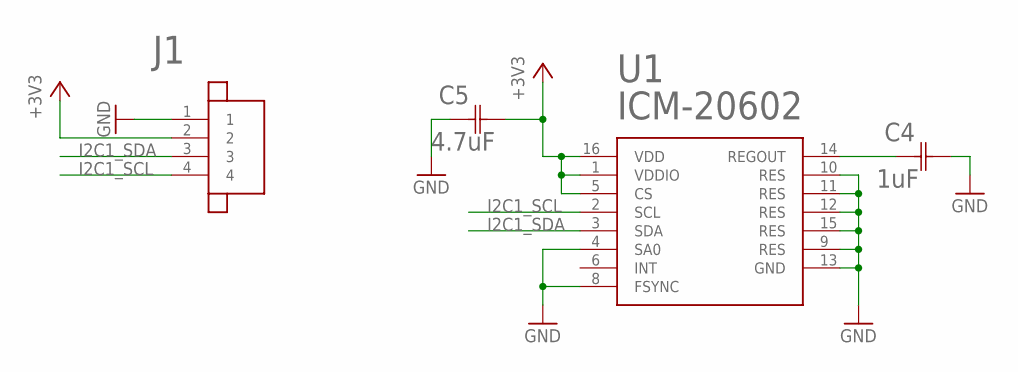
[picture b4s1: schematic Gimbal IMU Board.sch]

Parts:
C4: 1uF; YAG_CC0805
C5: 4.7uF; 0603-M
J1: JST_SH_4POS
U1: ICM-20602; 16LGA

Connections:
+3V3: C5.2, J1.2, U1.1 (VDDIO), U1.5 (CS), U1.16 (VDD)
GND: C4.2 (22), C5.1, J1.1, U1.4 (SA0), U1.8 (FSYNC), U1.9 (RES), U1.10 (RES), U1.11 (RES), U1.12 (RES), U1.13 (GND), U1.15 (RES)
I2C1_SCL: J1.4, U1.2 (SCL)
I2C1_SDA: J1.3, U1.3 (SDA)
unnamed: C4.1 (11), U1.14 (REGOUT)

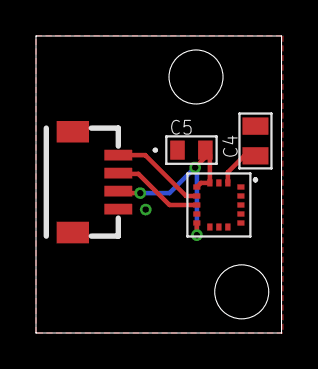
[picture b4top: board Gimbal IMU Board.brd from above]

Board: 2 copper layers, 13.6 x 16.5 mm, 4 parts (0 on the bottom side), 5 nets.

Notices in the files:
parts and their libraries:
SparkFun-Connectors: Licensing: Creative Commons ShareAlike 4.0 International - https://creativecommons.org/licenses/by-sa/4.0
COPYRIGHT: Copyright C 2015 Accelerated Designs. All rights reserved
